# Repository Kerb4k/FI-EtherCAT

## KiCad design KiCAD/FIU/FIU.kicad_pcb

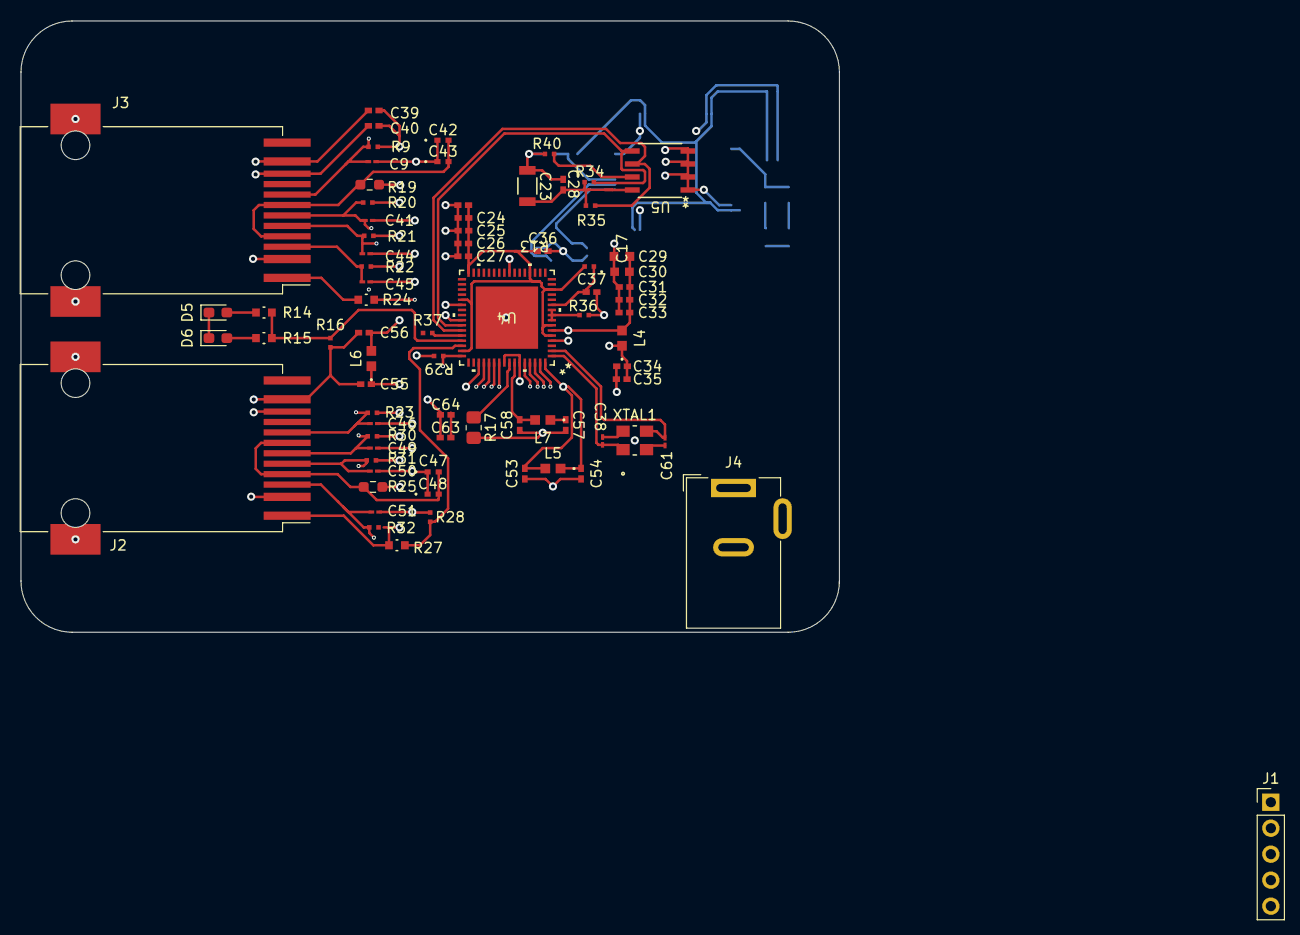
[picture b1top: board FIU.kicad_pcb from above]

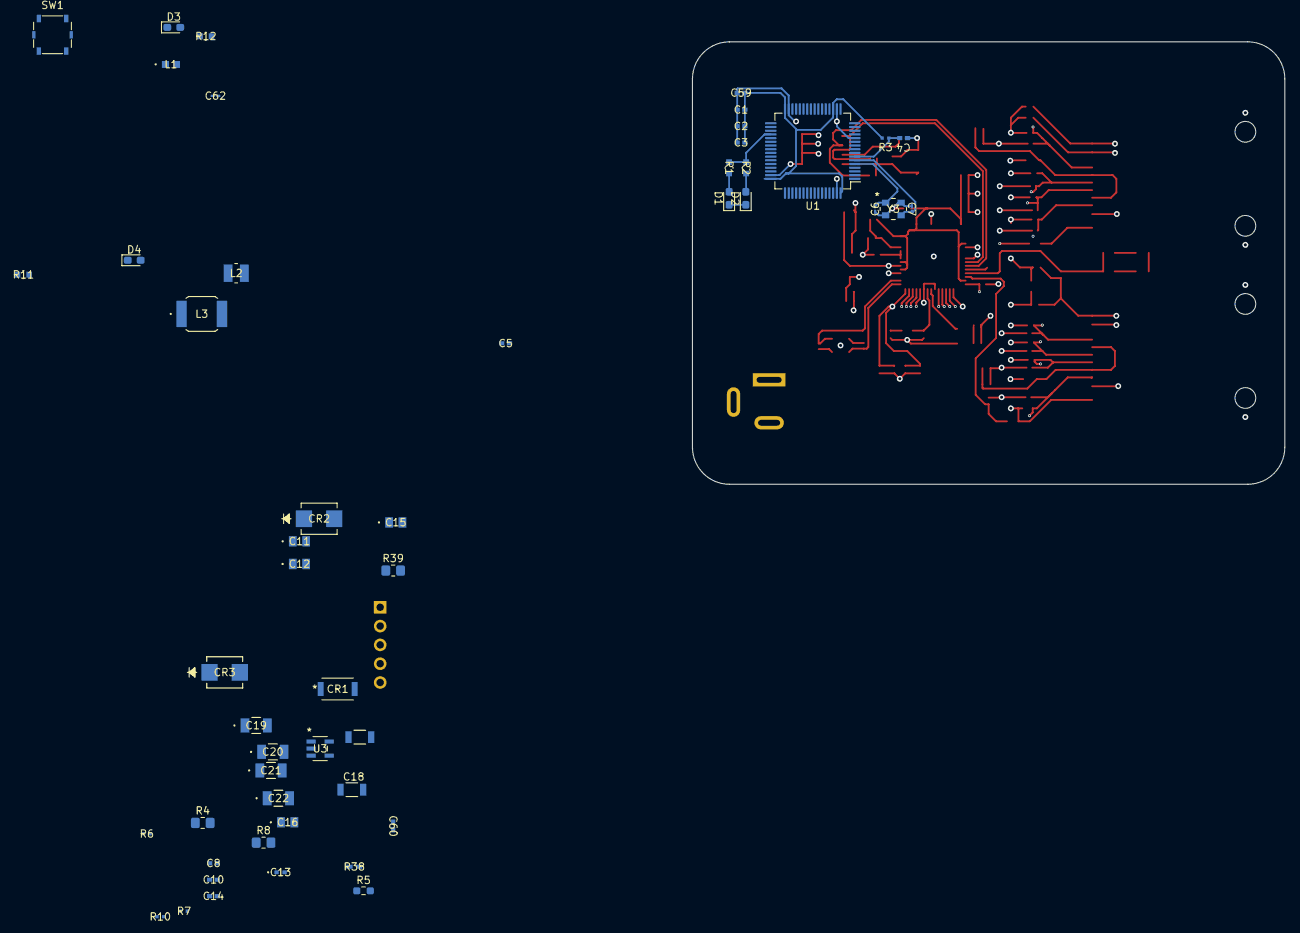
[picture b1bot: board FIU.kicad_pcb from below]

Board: 4 copper layers, 80.0 x 59.8 mm, 128 parts (51 on the bottom side), 59 nets.

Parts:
C1, C2, C3, C4, C5, C8, C10, C14, C17, C24, C25, C26, C27, C28, C31, C32, C33, C34, C35, C36, C37, C39, C40, C53, C54, C55, C56, C57, C58, C59, C60, C63, C64: 0.1uF; CAP_GRM155R71H104KE14J_MUR
C6, C7, C38, C61: 18pF; G-033_MUR
C9, C41, C44, C45, C46, C49, C50, C51, C62: 15pF; G-033_MUR
C11, C12, C15, C16: 4.7uF; CAP_GRM21_2p15X1p4X1p4_MUR
C13, C42, C43, C47, C48: 22nF; G-155_MUR
C18, C23, C52: 2.2uF; CAP_CL31_SAM
C19, C20, C21, C22: 10uF; CAP_UMK316BBJ106ML-T_TAY
C29: 1uF; CAP_GRT188R61H105KE13D_MUR
C30: 220pF; G-188_MUR
CR1: PMEG3050EP_115; SDO_CFP5_SOD128_NEX
CR2, CR3: STTH4R02U; SMB_STM
D1, D2: LED; LED_0603_1608Metric_Pad1.05x0.95mm_HandSolder
D3, D4, D5, D6: Green; LED_0603_1608Metric_Pad1.05x0.95mm_HandSolder
J1: Conn_01x05; PinHeader_1x05_P2.54mm_Vertical
J2, J3: RJ45_Wuerth_74980111211; RJ45_Wuerth_74980111211_Horizontal
J4: Barrel_Jack; BarrelJack_Wuerth_6941xx301002
L1, L4, L5, L6, L7: BLM18PG330SN1D; IND_BLM18_0603_MUR
L2: 2.2uH; IND_SRN2512_BRN
L3: 10uH; IND_IDC-2512_VIS
R1, R2, R11, R12, R14, R15, R24, R27: 470; RC0603N_PAN
R3, R13, R16, R28, R29, R34, R35, R36, R37, R40: 4.75k; RC0402N_PAN-L
R4: 110K; R_0805_2012Metric_Pad1.20x1.40mm_HandSolder
R5: 0.05; R_0603_1608Metric_Pad0.98x0.95mm_HandSolder
R6, R7, R10: 10k; RC0402N_PAN-L
R8: 100K; R_0805_2012Metric_Pad1.20x1.40mm_HandSolder
R9, R20, R21, R22, R23, R30, R31, R32: 49.9; RC0402N_PAN-L
R17: 12k1; R_0805_2012Metric_Pad1.20x1.40mm_HandSolder
R19, R25: 10; R_0603_1608Metric_Pad0.98x0.95mm_HandSolder
R38: 45k3; RC0402N_PAN-M
R39: 1.5k; R_0805_2012Metric_Pad1.20x1.40mm_HandSolder
SW1: SW_Push_Open_Dual; SW_SPST_Panasonic_EVQPL_3PL_5PL_PT_A15
U1: STM32F303RETx; LQFP-64_10x10mm_P0.5mm
U3: LMR10510XMFE/NOPB; MF05A
U4: LAN9252/ML; QFN64_ML_MCH
U5: M24C16-WMN6P; SO8N_4X5X1P27_STM
XTAL1: 25Mhz; ECX-32_SMDXTAL_ECS
Y3: 12Mhz; CRYSTAL_ABM8G_ABR

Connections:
+3.3V: C1.2, C2.2, C3.2, C59.2, L1.1, R3.1, U1.19 (VDD), U1.32 (VDD), U1.48 (VDD), U1.64 (VDD)
+3V3A: C39.2, C40.2, C55.2, C56.2, L6.1, L6.2, R9.1, R19.1, R20.1, R21.1, R22.1, U4.51 (VDD33TXRX1)
+3V3B: C53.2, C54.2, C63.2, C64.2, L5.1, L5.2, R23.1, R25.1, R30.1, R31.1, R32.1, U4.64 (VDD33TXRX2)
+5V: C10.2, C15.2, C16.2, C19.2, C20.2, C52.2, L3.1, R6.1, R8.1, U3.5 (VIN)
/UART1_RX: J1.4, U1.43 (PA10)
/UART1_TX: J1.3, U1.42 (PA9)
BOOT: R39.1, SW1.1, U1.60 (BOOT0)
GND: C1.1, C2.1, C3.1, C4.1, C5.1, C6.1, C7.1, C8.1, C9.1, C10.1, C11.1, C12.1, C13.1, C15.1, C16.1, C17.1, C18.1, C19.1, C20.1, C21.1, C22.1, C23.1, C24.1, C25.1, C26.1, C27.1, C28.1, C29.1, C30.1, C31.1, C32.1, C33.1, C34.1, C35.1, C36.1, C37.1, C38.1, C39.1, C40.1, C41.1, C42.1, C43.1, C44.1, C45.1, C46.1, C47.1, C48.1, C49.1, C50.1, C51.1, C52.1, C53.1, C54.1, C55.1, C56.1, C57.1, C58.1, C59.1, C60.2, C61.1, C62.1, C63.1, C64.1, CR1.2, D1.1 (K), D2.1 (K), D3.1 (K), D4.1 (K), D5.1 (K), D6.1 (K), J2.2, J2.10, J2.11, J2.SH, J3.2, J3.10, J3.11, J3.SH, J4.2, R5.2, R7.2, R10.2, R16.2, R17.2, R28.2, R29.2, R36.2, R39.2, R40.2, U1.12 (VSSA), U1.18 (VSS), U1.31 (VSS), U1.47 (VSS), U1.63 (VSS), U3.2 (GND), U4.4 (OSCVSS), U4.41 (TESTMODE), U4.65 (VSS), U5.1 (NC), U5.2 (NC), U5.3 (NC), U5.4 (VSS), XTAL1.2 (GND), XTAL1.4 (GND), Y3.2, Y3.4
IRQ: R37.2, U1.34 (PB13), U4.44 (IRQ)
LAN_SYNC0: U1.35 (PB14), U4.34 (SYNC0/LATCH0)
LAN_SYNC1: U1.26 (PB0), U4.18 (SYNC1/LATCH1)
unnamed: C60.1, CR3.1, J4.1
unnamed: D1.2 (A), R1.2
unnamed: D2.2 (A), R2.2
unnamed: D3.2 (A), R11.2
unnamed: D4.2 (A), R12.2
unnamed: D5.2 (A), R14.2
unnamed: D6.2 (A), R15.2
unnamed: J1.1, U1.46 (PA13)
unnamed: J1.2, U1.49 (PA14)
unnamed: J2.1, R27.1
unnamed: C47.2, C48.2, J2.4 (TCT), J2.7 (RCT), R25.2
unnamed: C49.2, J2.6 (RD+), R30.2, U4.60 (RXPB)
unnamed: C46.2, J2.8 (RD-), R23.2, U4.61 (RXNB)
unnamed: C51.2, J2.3 (TD+), R32.2, U4.62 (TXPB)
unnamed: C50.2, J2.5 (TD-), R31.2, U4.63 (TXNB)
unnamed: J3.1, R24.1
unnamed: C42.2, C43.2, J3.4 (TCT), J3.7 (RCT), R19.2
unnamed: C41.2, J3.6 (RD+), R20.2, U4.55 (RXPA)
unnamed: C9.2, J3.8 (RD-), R9.2, U4.54 (RXNA)
unnamed: C45.2, J3.3 (TD+), R22.2, U4.53 (TXPA)
unnamed: C44.2, J3.5 (TD-), R21.2, U4.52 (TXNA)
unnamed: R1.1, R2.1, U1.36 (PB15)
unnamed: C6.2, U1.5 (PF0), Y3.1
unnamed: C7.2, U1.6 (PF1), Y3.3
unnamed: C5.2, C62.2, L1.2, U1.13 (VDDA)
unnamed: CR2.1, R5.1
unnamed: R6.2, R7.1
unnamed: C14.1, CR2.2, L3.2
unnamed: C8.2, C11.2, C12.2, CR3.2, R4.1
unnamed: R8.2, U3.4 (EN)
unnamed: R10.1, R38.2, U3.3 (FB)
unnamed: CR1.1, L2.1, U3.1 (SW)
unnamed: R36.1, U4.8 (FXLOSEN), U4.9 (FXSDA/FXLOSA/FXSDENA), U4.10 (FXSDB/FXLOSB/FXSDENB)
unnamed: R24.2, R29.1, U4.48 (LINKACTLED0/TDO/CHIP_MODE0)
unnamed: R27.2, R28.1, U4.46 (LINKACTLED1/TDI/CHIP_MODE1)
unnamed: C38.2, U4.1 (OSCI), XTAL1.1 (CRYSTAL)
unnamed: C61.2, U4.2 (OSCO), XTAL1.3 (CRYSTAL)
unnamed: R17.1, U4.57 (RBIAS)
unnamed: C37.2, R13.2, U4.11 (RST#)
unnamed: R14.1, R15.1, R16.1, U4.45 (RUNLED/E2PSIZE)
unnamed: C58.2, L7.2, U4.58 (VDD33BIAS)
unnamed: R40.1, U5.7 (*WC)
RESET: C4.2, J1.5, R3.2, U1.7 (NRST)
TCK: R35.2, U4.43 (EESCL/TCK), U5.6 (SCL)
TMS: R34.2, U4.42 (EESDA/TMS), U5.5 (SDA)
VDD12TX: C34.2, C35.2, L4.1, U4.56 (VDD12TX1), U4.59 (VDD12TX2)
VDDCR: C29.2, C30.2, C31.2, C32.2, C33.2, L4.2, U4.6 (VDDCR), U4.24 (VDDCR), U4.38 (VDDCR)
VDDIO: C17.2, C18.2, C21.2, C22.2, C23.2, C24.2, C25.2, C26.2, C27.2, C28.2, C36.2, C57.2, L2.2, L7.1, R11.1, R12.1, R13.1, R34.1, R35.1, R37.1, R38.1, SW1.2, U4.5 (VDD33), U4.7 (REG_EN), U4.14 (VDDIO), U4.20 (VDDIO), U4.32 (VDDIO), U4.37 (VDDIO), U4.47 (VDDIO), U5.8 (VCC)

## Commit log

2023-11-03 some changes
2023-11-10 finished ethercat part
2023-11-12 new level
2023-11-19 updated libraries
2023-11-26 finished front of pcb
